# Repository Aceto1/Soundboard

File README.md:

An Arduino-based physical soundboard with a Windows Desktop GUI.

# Building the Soundboard

## Materials

- 1 Arduino board of your choice (e.g. ESP8266)

- 1 USB cable

- 1 CD74HC4067 analog 16 channel multiplexer

- 15 push-buttons

- Some sort of case (or like for my prototyp: two pieces of plywood with the appropriate holes and some spacers)

- Wire (I used 20AWG)

- Soldering iron

Begin by inserting the buttons into the case and connecting one pole of each button with wire and solder in series. After that, also connect the last one to a 3V output of your arduino.

Then connect the other side of each button to the appropriate channel of the multiplexer (starting top left with 0 and ending bottom right with 15).

Connect the pins of the multiplexer as follows to the arduino:

- S0: D5

- S1: D6

- S2: D7

- S3: D1

- SIG: A0

- EN: Leave it unconnected

# Installation

## Requirements

- [VB-Audio VoiceMeeter Banana](https://vb-audio.com/Voicemeeter/banana.htm) - for routing the playback into your VoIP Application of choice

- [CH341 Driver](www.wch.cn/download/CH341SER_ZIP.html) - or the equivalent driver for your Arduino board

- The latest binary of this repository

Install VoiceMeeter and the Driver, then reboot your PC. This will probably bork your sound settings in windows. We will fix that soon.

Now copy the Soundboard.exe and all other files that come with it to `C:\Programs Files\Soundboard\`.

Open VoiceMeeter Banana and firstly go to "Menu" at the top right and activate "Run on Windows Startup".

After that Click on "A1" and select your regular output device (speakers, headphones).

Click on "Hardware Input 1" and select your regular input device (microphone). Then only select "B1" below that.

Then, under "Virtual Inputs" just select "A1" below "VoiceMeeter VAIO" and just "B1" below "VoiceMeeter AUX".

Now go into the Windows sound settings and set "VoiceMeeter Input" as your default output device and "VoiceMeeter Output" as yout default input device.

Now connect your physical soundboard and start the application, you're all set.

# Usage

Choose the COM-Port of your Soundboard. This is usually the only or one of very few COM-Ports and can be trial-and-errored.

Click a button to change it's content (title/file). Configured files are kept in the folder they were in. That means should you delete or move a file you also need to change the setting of the button.

Should you wish to start this application with Windows, just activatt he toggle button. This creates a shortcut in your Autostart folder.

Minimizing the application moves it to the system tray. This is also where the application will be on startup.

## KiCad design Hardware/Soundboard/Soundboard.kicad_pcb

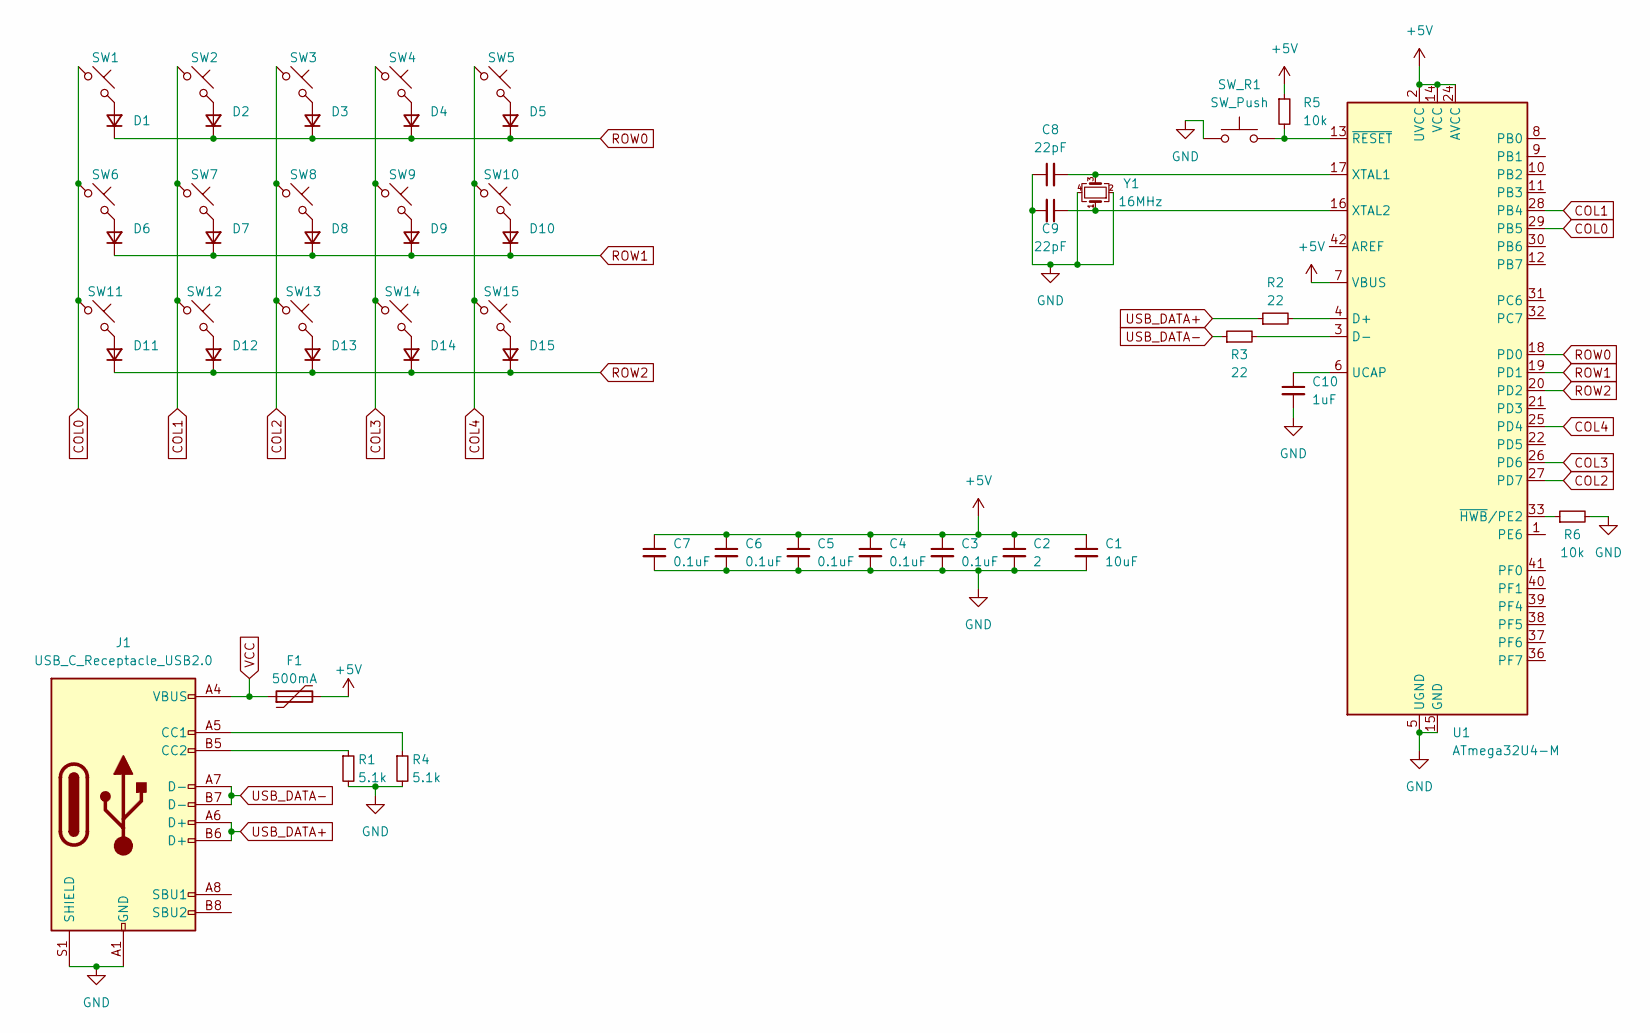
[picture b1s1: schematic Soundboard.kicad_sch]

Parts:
C1: 10uF; C_0805_2012Metric
C2: 2; C_0805_2012Metric
C3, C4, C5, C6, C7: 0.1uF; C_0805_2012Metric
C8, C9: 22pF; C_0805_2012Metric
C10: 1uF; C_0805_2012Metric
D1, D2, D3, D4, D5, D6, D7, D8, D9, D10, D11, D12, D13, D14, D15: D_Small; D_SOD-123
F1: 500mA; Fuse_1206_3216Metric
J1: USB_C_Receptacle_USB2.0; USB_C_Receptacle_HRO_TYPE-C-31-M-14
R1, R4: 5.1k; R_0805_2012Metric
R2, R3: 22; R_0805_2012Metric
R5, R6: 10k; R_0805_2012Metric
SW1, SW2, SW3, SW4, SW5, SW6, SW7, SW8, SW9, SW10, SW11, SW12, SW13, SW14, SW15: MX_SW_solder; SW_MX_1u
SW_R1: SW_Push; SW_SPST_SKQG_WithStem
U1: ATmega32U4-M; QFN-44-1EP_7x7mm_P0.5mm_EP5.2x5.2mm
Y1: 16MHz; Crystal_SMD_3225-4Pin_3.2x2.5mm

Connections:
+5V: C1.1, C2.1, C3.1, C4.1, C5.1, C6.1, C7.1, F1.2, R5.1, U1.2 (UVCC), U1.7 (VBUS), U1.14 (VCC), U1.24 (AVCC), U1.34 (VCC), U1.44 (AVCC)
COL0: SW1.1, SW6.1, SW11.1, U1.29 (PB5)
COL1: SW2.1, SW7.1, SW12.1, U1.28 (PB4)
COL2: SW3.1, SW8.1, SW13.1, U1.27 (PD7)
COL3: SW4.1, SW9.1, SW14.1, U1.26 (PD6)
COL4: SW5.1, SW10.1, SW15.1, U1.25 (PD4)
GND: C1.2, C2.2, C3.2, C4.2, C5.2, C6.2, C7.2, C8.1, C9.2, C10.2, J1.A1 (GND), J1.A12 (GND), J1.B1 (GND), J1.B12 (GND), J1.S1 (SHIELD), R1.2, R4.2, R6.2, SW_R1.1, U1.5 (UGND), U1.15 (GND), U1.23 (GND), U1.35 (GND), U1.43 (GND), U1.45 (GND), Y1.2, Y1.4
unnamed: C8.2, U1.17 (XTAL1), Y1.3
unnamed: C9.1, U1.16 (XTAL2), Y1.1
unnamed: C10.1, U1.6 (UCAP)
unnamed: D1.2 (A), SW1.2
unnamed: D2.2 (A), SW2.2
unnamed: D3.2 (A), SW3.2
unnamed: D4.2 (A), SW4.2
unnamed: D5.2 (A), SW5.2
unnamed: D6.2 (A), SW6.2
unnamed: D7.2 (A), SW7.2
unnamed: D8.2 (A), SW8.2
unnamed: D9.2 (A), SW9.2
unnamed: D10.2 (A), SW10.2
unnamed: D11.2 (A), SW11.2
unnamed: D12.2 (A), SW12.2
unnamed: D13.2 (A), SW13.2
unnamed: D14.2 (A), SW14.2
unnamed: D15.2 (A), SW15.2
unnamed: J1.A5 (CC1), R4.1
unnamed: J1.B5 (CC2), R1.1
unnamed: R3.2, U1.3 (D-)
unnamed: R2.2, U1.4 (D+)
unnamed: R5.2, SW_R1.2, U1.13 (~RESET)
unnamed: R6.1, U1.33 (~HWB/PE2)
ROW0: D1.1 (K), D2.1 (K), D3.1 (K), D4.1 (K), D5.1 (K), U1.18 (PD0)
ROW1: D6.1 (K), D7.1 (K), D8.1 (K), D9.1 (K), D10.1 (K), U1.19 (PD1)
ROW2: D11.1 (K), D12.1 (K), D13.1 (K), D14.1 (K), D15.1 (K), U1.20 (PD2)
USB_DATA+: J1.A6 (D+), J1.B6 (D+), R2.1
USB_DATA-: J1.A7 (D-), J1.B7 (D-), R3.1
VCC: F1.1, J1.A4 (VBUS), J1.A9 (VBUS), J1.B4 (VBUS), J1.B9 (VBUS)

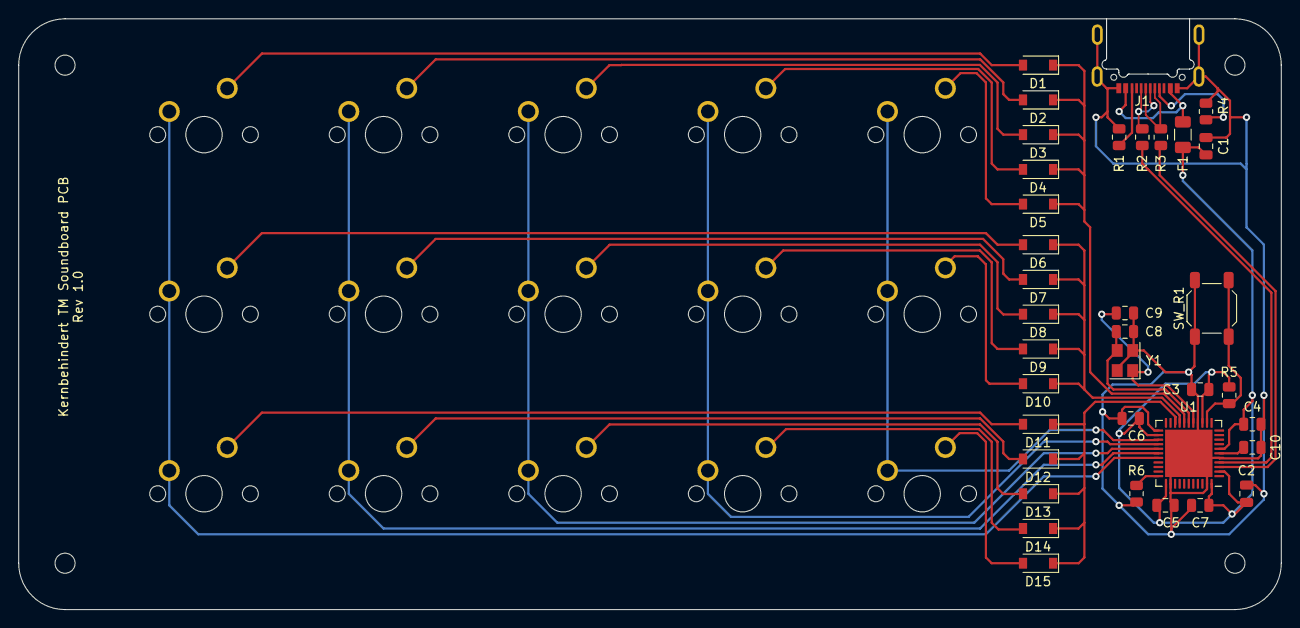
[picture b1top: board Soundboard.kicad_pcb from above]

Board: 2 copper layers, 138.4 x 64.8 mm, 55 parts (0 on the bottom side), 37 nets.

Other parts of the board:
REFM1, REFM2, REFM3, REFM4: M2; MountingHole_2.2mm_M2

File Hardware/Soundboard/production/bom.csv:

Designator,Footprint,Quantity,Value,LCSC Part #
C1,0805,1,10uF,
C10,0805,1,1uF,
C2,0805,1,2,
C3,0805,1,0.1uF,
C4,0805,1,0.1uF,
C5,0805,1,0.1uF,
C6,0805,1,0.1uF,
C7,0805,1,0.1uF,
C8,0805,1,22pF,
C9,0805,1,22pF,
"D1, D10, D11, D12, D13, D14, D15, D2, D3, D4, D5, D6, D7, D8, D9",D_SOD-123,15,D_Small,
F1,1206,1,500mA,
J1,USB_C_Receptacle_HRO_TYPE-C-31-M-14,1,USB_C_Receptacle_USB2.0,
R1,0805,1,5.1k,
R2,0805,1,22,
R3,0805,1,22,
R4,0805,1,5.1k,
R5,0805,1,10k,
R6,0805,1,10k,
"SW1, SW10, SW11, SW12, SW13, SW14, SW15, SW2, SW3, SW4, SW5, SW6, SW7, SW8, SW9",SW_MX_1u,15,MX_SW_solder,
SW_R1,SW_SPST_SKQG_WithStem,1,SW_Push,
U1,QFN-44-1EP_7x7mm_P0.5mm_EP5.2x5.2mm,1,ATmega32U4-M,
Y1,Crystal_SMD_3225-4Pin_3.2x2.5mm,1,16MHz,

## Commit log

2022-02-01 [fix] config.json is now saved to ProgramData folder to avoid missing permissions
2022-02-01 [feat] Stop playback when pressing the same button
2022-02-01 [fix] Translate strings to english
2022-02-01 [feat] Add README
2022-10-10 Enable usage without physical soundboard
2023-02-13 Bugfix
2023-02-13 Update to .NET 7
2023-02-20 PCB rev 0.1
